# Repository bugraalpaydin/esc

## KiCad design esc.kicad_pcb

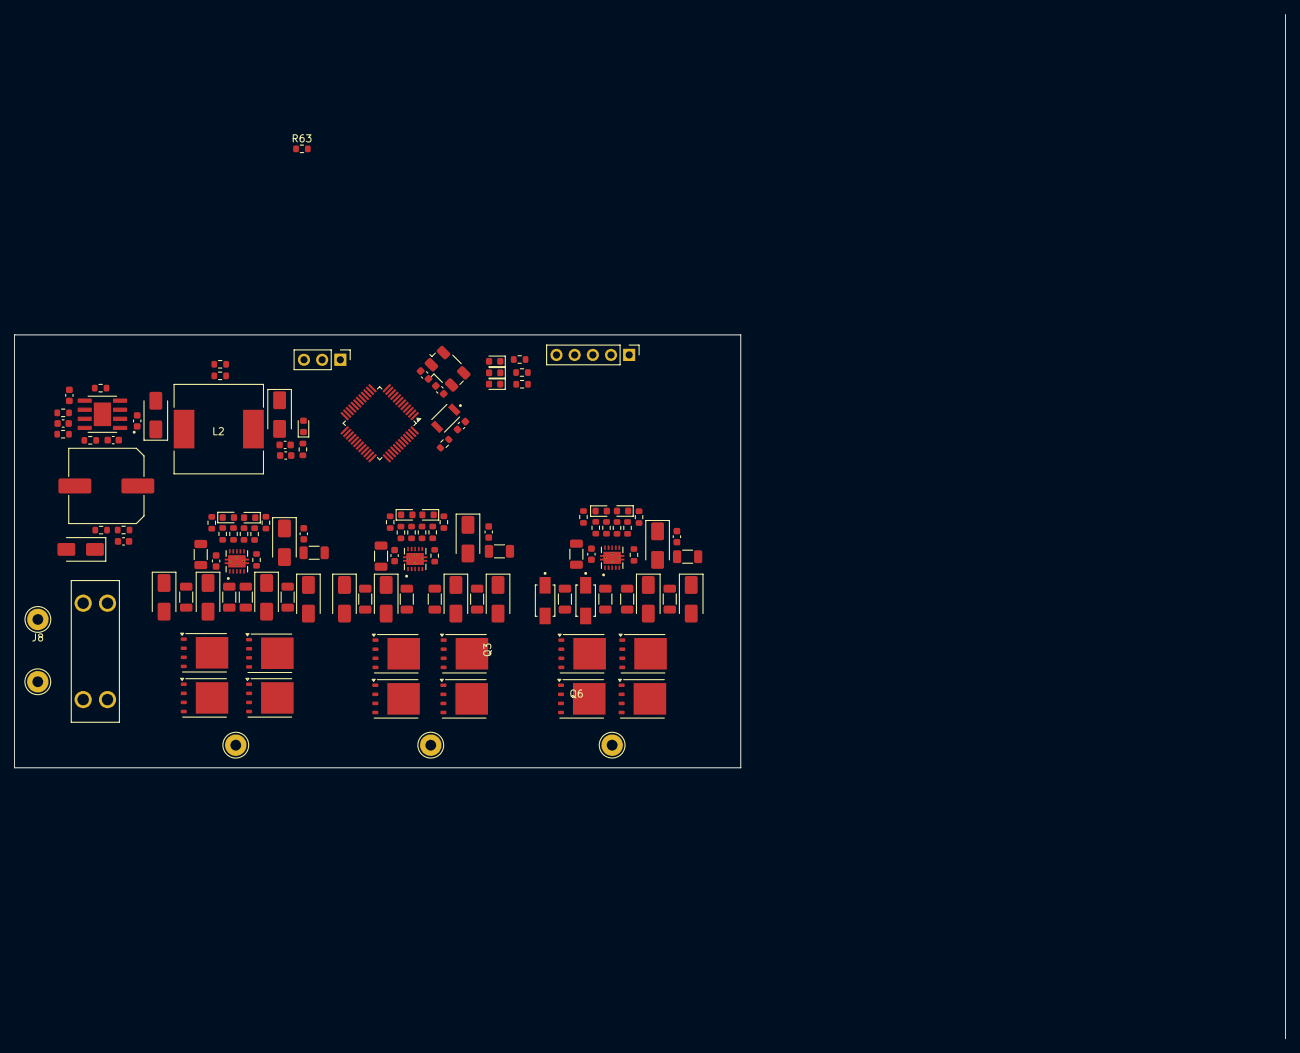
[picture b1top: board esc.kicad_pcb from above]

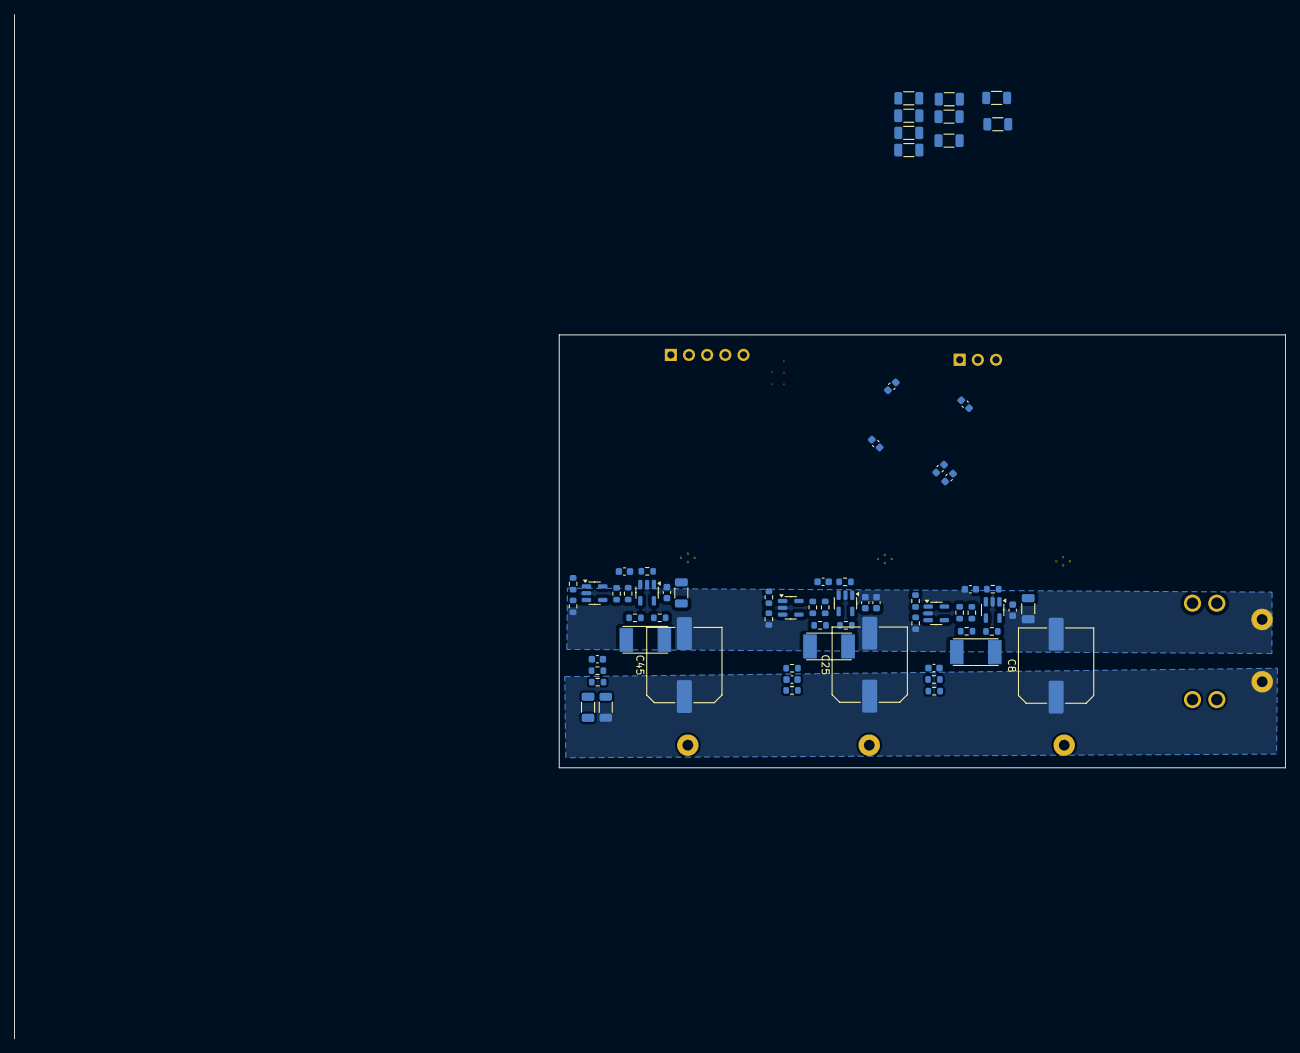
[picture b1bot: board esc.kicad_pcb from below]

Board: 2 copper layers, 101.5 x 60.5 mm, 193 parts (67 on the bottom side), 109 nets.

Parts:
C1: 220uF_Electrolyt; C_Elec_10x10.2
C2: 2.2u; C_1206_3216Metric
C3, C5, C9, C13, C15, C17, C18, C20, C21, C34, C36, C37, C39, C41, C52: 100n_603; C_0603_1608Metric
C4, C14: 4.7u_1206; C_1206_3216Metric
C6, C7, C23, C24: 100n; C_0603_1608Metric
C8, C25, C45: 330uF; C_Elec_10x10.2
C10, C42, C53: C_Snubber_603; C_1206_3216Metric
C11, C16, C38: C_Snubber; C_1206_3216Metric
C12, C31: 2.2u_1206; C_1206_3216Metric
C19: 1n_603; C_0603_1608Metric
C22, C29, C44, C54: 10n_603; C_0603_1608Metric
C26: 10u; C_0603_1608Metric
C27, C28: 22p; C_0603_1608Metric
C30: 4.7u_Electrolyt; C_1206_3216Metric
C32: 10u_603; C_0603_1608Metric
C33: 47u_603; C_0603_1608Metric
C35, C40: 1u_603; C_1206_3216Metric
C43: 100nF_603; C_0603_1608Metric
C51: 1u_603; C_0603_1608Metric
D1, D2, D3, D4, D5, D6, D8, D11, D12, D14, D16, D17, D18, D20, D26, D29: CDBA540-HF; D_SMA
D7, D13: CDBA540-HF; ES1J_Diode
D9: PWR_LED; LED_0603_1608Metric
D15, D21, D22, D25: Red_LED; LED_0603_1608Metric
D19, D23, D24, D27: Blue_LED; LED_0603_1608Metric
D28: Green_LED; LED_0603_1608Metric
F1: Fuse; FUSE_3557-2
J1: Conn_01x05_Socket; PinHeader_1x05_P2.54mm_Vertical
J2: Conn_01x03_Socket; PinHeader_1x03_P2.54mm_Vertical
J5, J6, J7, J8, J9: Conn_01x01_Pin; Pin_D1.3mm_L11.0mm_LooseFit
L2: 33uH; SSR1210-330M
Q1, Q2, Q3, Q4, Q5, Q6, Q7, Q8, Q9, Q10, Q11, Q12: FDMS86550; TDSON-8-1
R1: 47k_603; R_0603_1608Metric
R2: 4.7k_603; R_0603_1608Metric
R3, R4, R5, R12, R13, R14, R19, R23, R25, R26, R36, R37, R44, R45, R46, R64, R65, R66, R86, R87, R88: 10k_603; R_0603_1608Metric
R6, R62, R84: 47R_603; R_0603_1608Metric
R7, R20, R21, R33, R34, R55, R56, R67, R68, R69, R70, R77, R78, R89, R90, R91, R92, R93, R94: 1k_603; R_0603_1608Metric
R8, R85: R_Snubber_603; R_1206_3216Metric
R9, R59, R81: R_Snubber; R_1206_3216Metric
R10, R11: 33R_603; R_0603_1608Metric
R15, R22, R30, R38, R39, R47, R50, R51, R58, R73, R74, R80: 22R_1206; R_1206_3216Metric
R16: 31.6k_603; R_0603_1608Metric
R17, R29, R42, R43: 22R_603; R_0603_1608Metric
R18, R35, R57, R60, R79, R82: 56k_603; R_0603_1608Metric
R24: 110k_603; R_0603_1608Metric
R27: 37k4_603; R_0603_1608Metric
R28, R49, R72: 1mR_3920_5W; BVT _2512_Shunt
R52: 10K_603; R_0603_1608Metric
R63: R_Snubber_603; R_0603_1608Metric
S8: MCU RESET; B3U-1000P
U1: STM32F103C8Tx; LQFP-48_7x7mm_P0.5mm
U2: AOZ1284PI; AOZ12894pı
U3, U7, U8, U10, U11, U12: TLV9061xDBV; SOT-23-5
U4, U5, U6: UCC27282DRCT; UCC27282
Y1: 8Mhz; Crystal_SMD_Abracon_ABM3B-4Pin_5.0x3.2mm

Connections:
+3V3: C6.1, C7.1, C23.1, C24.1, C26.1, D9.2 (A), D29.1 (K), J1.1, R16.1, R52.1, U1.1 (VBAT), U1.9 (VDDA), U1.24 (VDD), U1.36 (VDD), U1.48 (VDD)
+3v3: C17.1, C35.1, C36.1, C39.1, C40.1, C51.1, R36.2, R65.2, R87.2, U3.5 (V+), U7.5 (V+), U8.5 (V+), U10.5 (V+), U11.5 (V+), U12.5 (V+)
GND: C1.1, C3.2, C4.2, C5.2, C8.2, C9.2, C13.2, C14.2, C15.2, C17.2, C18.1, C20.2, C21.2, C22.2, C25.2, C29.2, C30.2, C32.2, C33.2, C35.2, C36.2, C37.2, C39.2, C40.2, C41.2, C44.2, C45.2, C51.2, C52.2, C54.2, D1.2 (A), D11.2 (A), J1.3, J2.3, J8.1, R2.2, R3.2, R4.1, R5.1, R12.2, R13.1, R14.1, R20.1, R21.2, R23.2, R25.2, R26.2, R27.2, R37.1, R44.2, R45.1, R46.1, R64.1, R67.1, R69.2, R70.2, R86.1, R89.1, R91.2, R92.2, R93.2, R94.2, U1.44 (BOOT0), U2.3 (GND), U3.2 (V-), U4.9 (VSS), U4.11 (THERMALPAD), U5.9 (VSS), U5.11 (THERMALPAD), U6.9 (VSS), U6.11 (THERMALPAD), U7.2 (V-), U8.2 (V-), U10.2 (V-), U11.2 (V-), U12.2 (V-)
HIN_A: D19.2 (A), R42.1, U1.29 (PA8)
HIN_B: D23.2 (A), R10.1, U1.30 (PA9)
HIN_C: D24.2 (A), R4.2, R17.1, U1.31 (PA10)
I_SENSE_A: C41.1, R62.2
I_SENSE_B: C52.1, R84.2
I_SENSE_C: C21.1, R6.2
LIN_A: D21.2 (A), R43.1, U1.17 (PA7), U1.26 (PB13)
LIN_B: D25.2 (A), R11.1, U1.27 (PB14)
LIN_C: D22.2 (A), R5.2, R29.1, U1.28 (PB15)
MCU_GND: C6.2, C7.2, C23.2, C24.2, C26.2, C27.2, C28.2, C43.2, R7.2, R68.2, R90.2, S8.1, U1.8 (VSSA), U1.23 (VSS), U1.35 (VSS), U1.47 (VSS)
MCU_RST: C43.1, J1.5, R52.2, S8.2, U1.7 (NRST)
MCU_SWCLK: J1.2, U1.37 (PA14)
MCU_SWDIO: J1.4, U1.34 (PA13)
unnamed: C10.1, R8.2
unnamed: C11.2, R9.1
unnamed: C16.2, R81.1
unnamed: C19.2, R27.1
unnamed: C38.2, R59.1
unnamed: C42.1, R63.2
unnamed: C53.1, R85.2
unnamed: C3.1, C31.1, D2.1 (K)
unnamed: D3.2 (A), Q1.4 (G), R30.2
unnamed: C2.1, C20.1, D4.1 (K)
unnamed: D5.2 (A), Q2.4 (G), R73.2
unnamed: D6.2 (A), Q3.4 (G), R74.2
unnamed: D7.2 (A), Q7.4 (G), R22.2
unnamed: D8.2 (A), Q4.4 (G), R38.2
unnamed: D9.1 (K), R21.1
unnamed: C34.2, D11.1 (K), L2.1, U2.1 (LX)
unnamed: D12.2 (A), Q8.4 (G), R15.2
unnamed: D13.2 (A), Q6.4 (G), R39.2
unnamed: D14.2 (A), Q9.4 (G), R47.2
unnamed: D15.1 (K), R7.1
unnamed: D16.2 (A), Q10.4 (G), R50.2
unnamed: D17.2 (A), Q11.4 (G), R51.2
unnamed: D18.2 (A), Q5.4 (G), R80.2
unnamed: D19.1 (K), R93.1
unnamed: D20.2 (A), Q12.4 (G), R58.2
unnamed: D21.1 (K), R94.1
unnamed: D22.1 (K), R70.1
unnamed: D23.1 (K), R91.1
unnamed: D24.1 (K), R69.1
unnamed: D25.1 (K), R92.1
unnamed: C12.1, C13.1, D26.1 (K)
unnamed: D27.1 (K), R68.1
unnamed: D28.1 (K), R90.1
unnamed: C32.1, C33.1, D29.2 (A), L2.2
unnamed: Q1.1 (S), Q1.2 (S), Q1.3 (S), Q3.1 (S), Q3.2 (S), Q3.3 (S), R72.1, R81.2
unnamed: Q4.1 (S), Q4.2 (S), Q4.3 (S), Q8.1 (S), Q8.2 (S), Q8.3 (S), R9.2, R28.1
unnamed: Q9.1 (S), Q9.2 (S), Q9.3 (S), Q11.1 (S), Q11.2 (S), Q11.3 (S), R49.1, R59.2
unnamed: R6.1, R18.2, U12.1
unnamed: R60.2, R62.1, U7.1
unnamed: R82.2, R84.1, U10.1
unnamed: C27.1, U1.5 (PD0), Y1.2
unnamed: C28.1, U1.6 (PD1), Y1.1
unnamed: C34.1, U2.2 (BST)
unnamed: C19.1, U2.5 (COMP)
unnamed: R24.2, R25.1, U2.8 (EN)
unnamed: R16.2, R23.1, U2.6 (FB)
unnamed: R26.1, U2.4 (FSW)
unnamed: C18.2, U2.7 (SS)
unnamed: R36.1, R37.2, U3.3 (+)
unnamed: R42.2, R45.2, U4.7 (HI)
unnamed: R43.2, R46.2, U4.8 (LI)
unnamed: R17.2, U5.7 (HI)
unnamed: R29.2, U5.8 (LI)
unnamed: R10.2, R13.2, U6.7 (HI)
unnamed: R11.2, R14.2, U6.8 (LI)
unnamed: R55.2, R57.1, U7.3 (+)
unnamed: R56.2, R60.1, U7.4 (-)
unnamed: R64.2, R65.1, U8.3 (+)
unnamed: R77.2, R79.1, U10.3 (+)
unnamed: R78.2, R82.1, U10.4 (-)
unnamed: R86.2, R87.1, U11.3 (+)
unnamed: R33.2, R35.1, U12.3 (+)
unnamed: R18.1, R34.2, U12.4 (-)
Phase_A_En: R44.1, U1.18 (PB0), U4.6 (EN)
Phase_A_HO: D16.1 (K), D20.1 (K), R50.1, R58.1, U4.4 (HO)
Phase_A_LO: D14.1 (K), D17.1 (K), R47.1, R51.1, U4.10 (LO)
Phase_A_Opamp+: R49.2, R55.1
Phase_A_Opamp-: R56.1, R78.1
Phase_B_En: R12.1, U1.19 (PB1), U6.6 (EN)
Phase_B_HO: D5.1 (K), D18.1 (K), R73.1, R80.1, U6.4 (HO)
Phase_B_LO: D3.1 (K), D6.1 (K), R30.1, R74.1, U6.10 (LO)
Phase_B_Opamp+: R72.2, R77.1
Phase_C_En: R3.1, U1.20 (PB2), U5.6 (EN)
Phase_C_HO: D7.1 (K), D13.1 (K), R22.1, R39.1, U5.4 (HO)
Phase_C_LO: D8.1 (K), D12.1 (K), R15.1, R38.1, U5.10 (LO)
Phase_C_Opamp+: R28.2, R33.1
User_LED_1: D15.2 (A), U1.39 (PB3)
User_LED_2: D28.2 (A), U1.40 (PB4)
User_LED_3: D27.2 (A), U1.41 (PB5)
User_UART_Rx: J2.2, U1.43 (PB7)
User_UART_Tx: J2.1, U1.42 (PB6)
VCC: C4.1, C5.1, C8.1, C14.1, C15.1, C25.1, C30.1, C37.1, C45.1, D2.2 (A), D4.2 (A), D26.2 (A), J9.1, Q2.5 (D), Q5.5 (D), Q6.5 (D), Q7.5 (D), Q10.5 (D), Q12.5 (D), R8.1, R63.1, R85.1, U4.1 (VDD), U4.3 (HB), U5.1 (VDD), U5.3 (HB), U6.1 (VDD), U6.3 (HB)
VCC_Sense: C29.1, R1.2, R2.1, U1.16 (PA6)
VIN: C1.2, C9.1, D1.1 (K), R1.1, R24.1, U2.9 (VIN)
VPH_A: C2.2, C38.1, C42.2, J7.1, Q9.5 (D), Q10.1 (S), Q10.2 (S), Q10.3 (S), Q11.5 (D), Q12.1 (S), Q12.2 (S), Q12.3 (S), R66.2, U4.5 (HS)
VPH_B: C12.2, C16.1, C53.2, J6.1, Q1.5 (D), Q2.1 (S), Q2.2 (S), Q2.3 (S), Q3.5 (D), Q5.1 (S), Q5.2 (S), Q5.3 (S), R88.2, U6.5 (HS)
VPH_C: C10.2, C11.1, C31.2, J5.1, Q4.5 (D), Q6.1 (S), Q6.2 (S), Q6.3 (S), Q7.1 (S), Q7.2 (S), Q7.3 (S), Q8.5 (D), R19.2, U5.5 (HS)
V_SENSE_A: C44.1, R66.1, R67.2
V_SENSE_B: C54.1, R88.1, R89.2
V_SENSE_C: C22.1, R19.1, R20.2
Vref_A: R57.2, U8.1, U8.4 (-)
Vref_C: R35.2, U3.1, U3.4 (-)
Vref_b: R79.2, U11.1, U11.4 (-)

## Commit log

2026-01-30 init
2026-01-30 init 2
2026-01-31 bitti sayılır
